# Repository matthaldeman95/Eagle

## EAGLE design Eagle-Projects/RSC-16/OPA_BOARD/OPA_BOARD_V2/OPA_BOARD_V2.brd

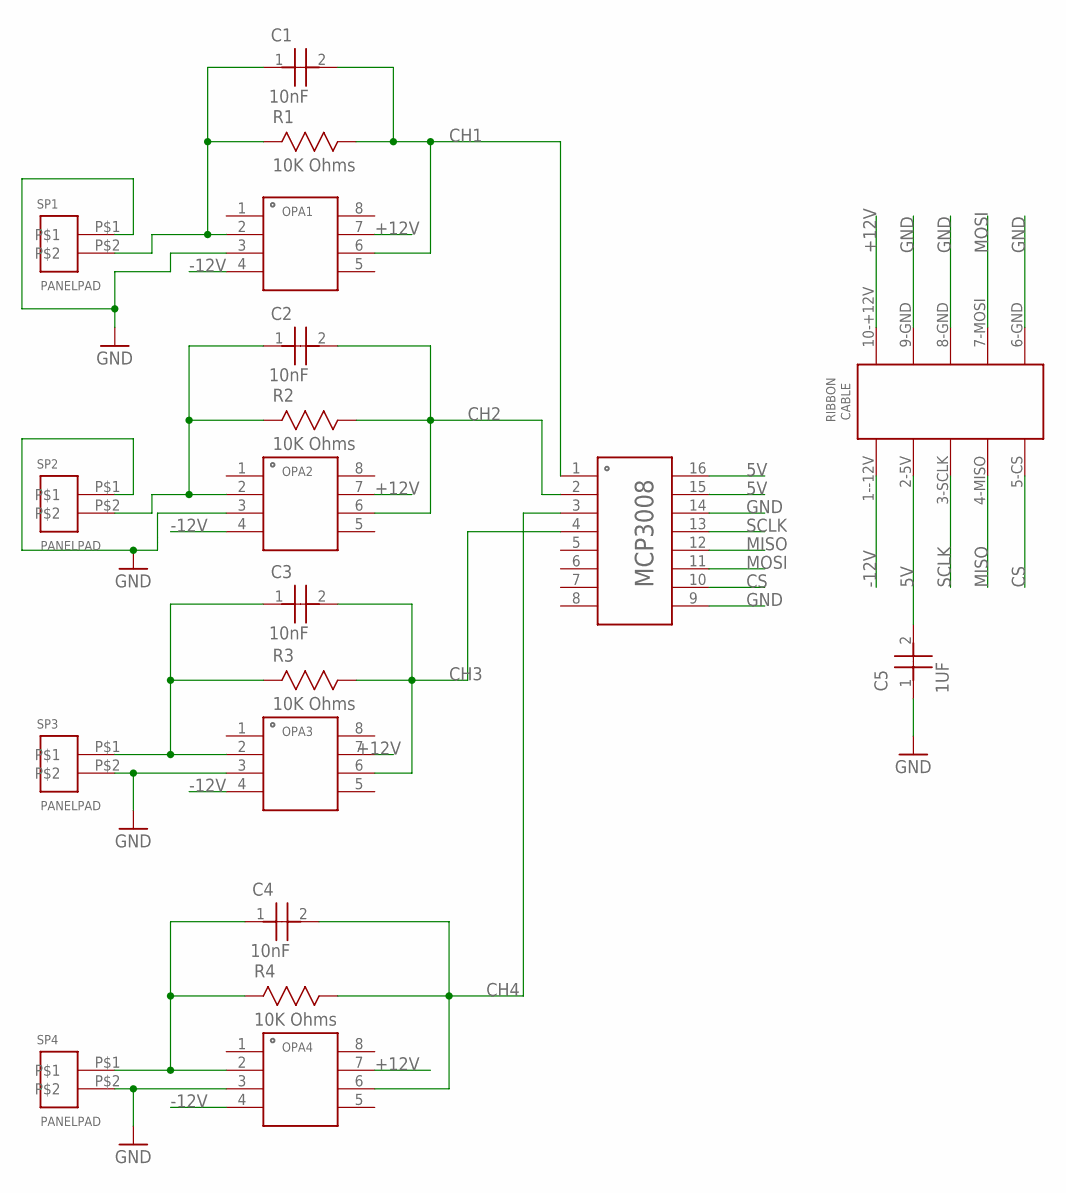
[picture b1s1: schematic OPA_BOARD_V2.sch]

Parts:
ADC: MCP3008-SOIC16; SOIC16N
C1, C2, C3, C4: 10nF; CAP1206
C5: 1UF; CAP1206
OPA1, OPA2, OPA3, OPA4: THS4631-SOIC8; SOIC8
R1, R2, R3, R4: 10K Ohms; RES1206
SP1, SP2, SP3, SP4: PANELPAD; PANELPADS
U$1: 5X2RIBBONCONNECTOR

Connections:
5V: ADC.15 (15-VREF), ADC.16 (16-VDD), C5.2, U$1.2-5V
+12V: OPA1.7 (7-VS+), OPA2.7 (7-VS+), OPA3.7 (7-VS+), OPA4.7 (7-VS+), U$1.10-+12V
-12V: OPA1.4 (4-VS-), OPA2.4 (4-VS-), OPA3.4 (4-VS-), OPA4.4 (4-VS-), U$1.1--12V
CH1: ADC.1 (1-CH0), C1.2, OPA1.6 (6-VOUT), R1.1
CH2: ADC.2 (2-CH1), C2.2, OPA2.6 (6-VOUT), R2.1
CH3: ADC.4 (4-CH3), C3.2, OPA3.6 (6-VOUT), R3.1
CH4: ADC.3 (3-CH2), C4.2, OPA4.6 (6-VOUT), R4.1
CS: ADC.10 (10-CS), U$1.5-CS
GND: ADC.9 (9-DGND), ADC.14 (14-AGND), C5.1, OPA1.3 (3-VIN+), OPA2.3 (3-VIN+), OPA3.3 (3-VIN+), OPA4.3 (3-VIN+), SP1.P$1, SP2.P$1, SP3.P$2, SP4.P$2, U$1.6-GND, U$1.8-GND, U$1.9-GND
MISO: ADC.12 (12-DOUT), U$1.4-MISO
MOSI: ADC.11 (11-DIN), U$1.7-MOSI
unnamed: C3.1, OPA3.2 (2-VIN-), R3.2, SP3.P$1
unnamed: C4.1, OPA4.2 (2-VIN-), R4.2, SP4.P$1
unnamed: C2.1, OPA2.2 (2-VIN-), R2.2, SP2.P$2
unnamed: C1.1, OPA1.2 (2-VIN-), R1.2, SP1.P$2
SCLK: ADC.13 (13-CLK), U$1.3-SCLK

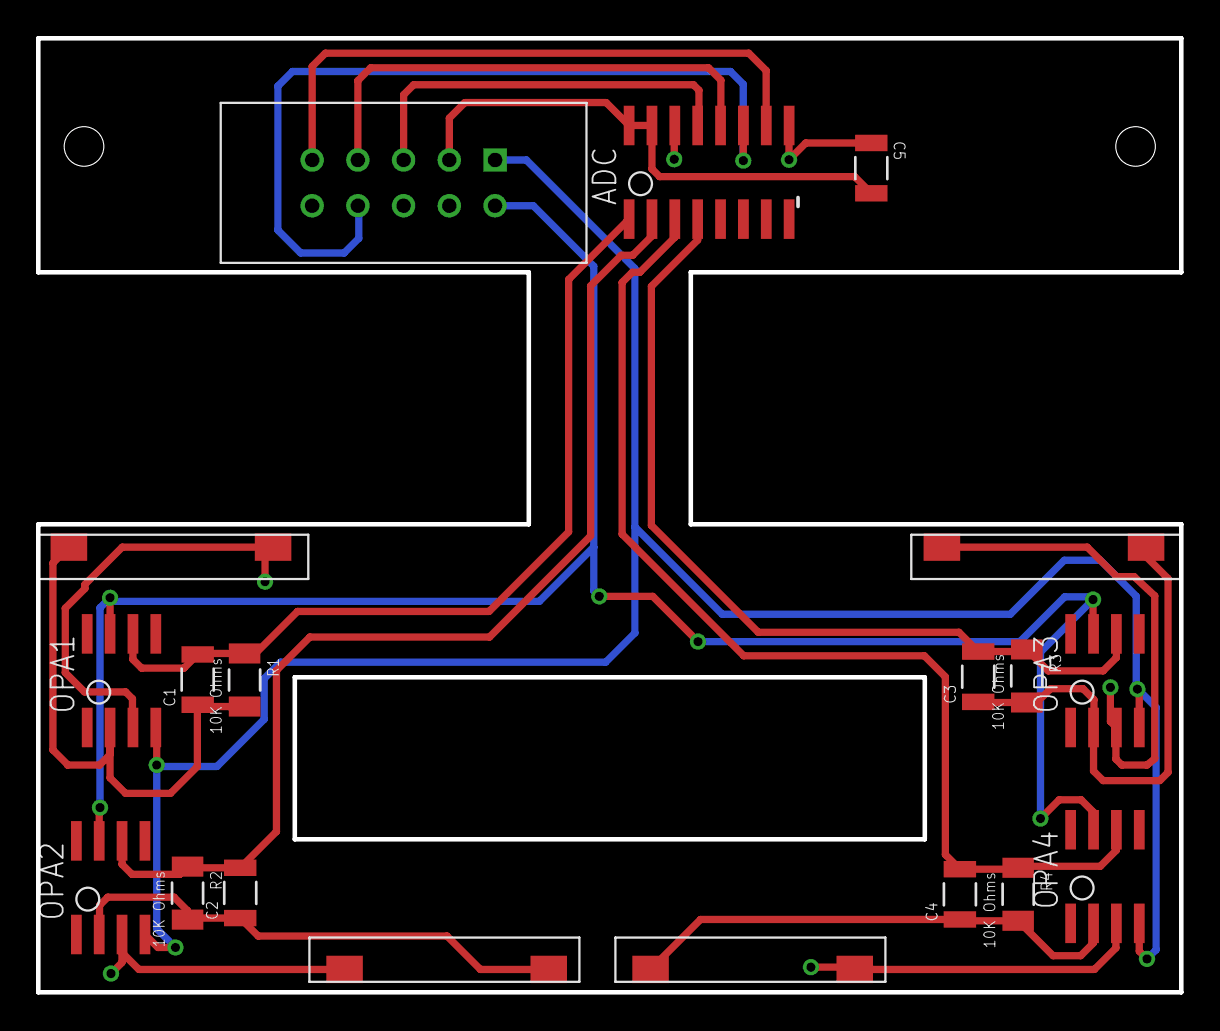
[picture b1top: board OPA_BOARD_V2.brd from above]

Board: 2 copper layers, 63.5 x 53.0 mm, 19 parts (0 on the bottom side), 16 nets.

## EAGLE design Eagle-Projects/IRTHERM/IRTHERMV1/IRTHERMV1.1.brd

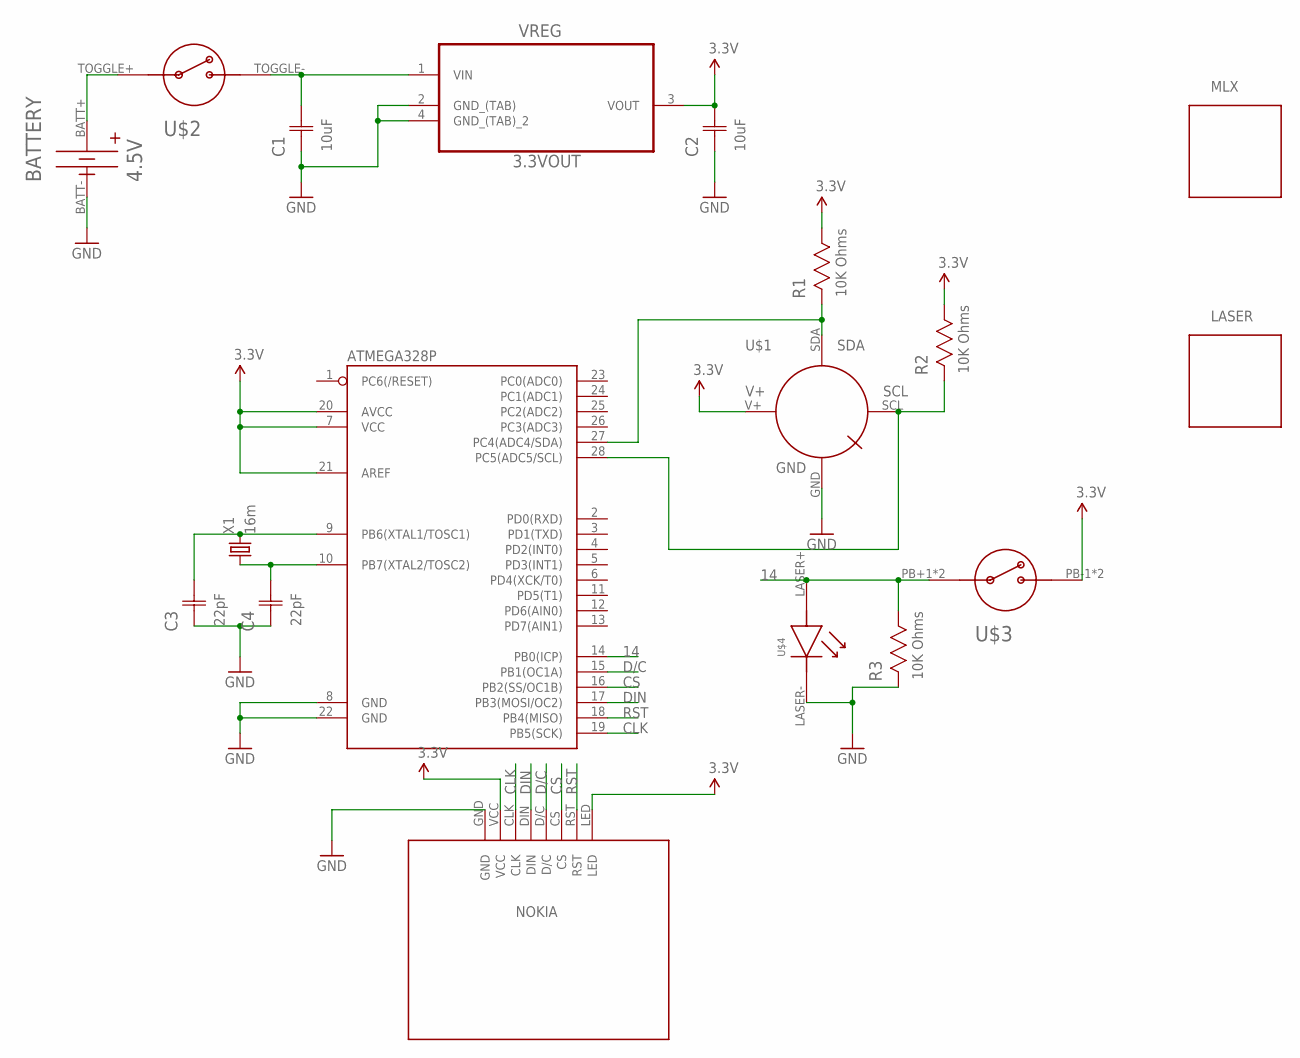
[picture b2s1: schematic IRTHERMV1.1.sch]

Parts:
ATMEGA328P: ATMEGA328P_PDIP; DIL28-3
BATTERY: 4.5V; KEYSTONE2479
C1, C2: 10uF; CAPC3216X180N
C3, C4: 22pF; CAPC3216X88N
LASER: KEYSTONECLIP; KEYSTONE50
MLX: KEYSTONECLIP; KEYSTONE50
R1, R2, R3: 10K Ohms; RESC3216X71N
U$1: MLX90614
U$2: 1683ON-OFFTOGGLE
U$3: 1009PUSHBUTTON
U$4: LASER
U$5: NOKIA
VREG: 3.3VOUT; SOT230P700X180-4N
X1: 16m; HC49US

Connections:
3.3V: ATMEGA328P.7 (VCC), ATMEGA328P.20 (AVCC), ATMEGA328P.21 (AREF), C2.2 (C2), R1.1, R2.1, U$1.V+ (MLXV+), U$3.PB-1 (ONOFF-), U$3.PB-2 (ONOFF-), U$5.LED, U$5.VCC, VREG.3 (VOUT)
14: ATMEGA328P.14 (PB0(ICP)), R3.1, U$3.PB+1 (ONOFF+), U$3.PB+2 (ONOFF+), U$4.LASER+
CLK: ATMEGA328P.19 (PB5(SCK)), U$5.CLK
CS: ATMEGA328P.16 (PB2(SS/OC1B)), U$5.CS
D/C: ATMEGA328P.15 (PB1(OC1A)), U$5.D/C
DIN: ATMEGA328P.17 (PB3(MOSI/OC2)), U$5.DIN
GND: ATMEGA328P.8 (GND), ATMEGA328P.22 (GND), BATTERY.BATT-, C1.1 (C1), C2.1 (C1), C3.1 (C1), C4.1 (C1), R3.2, U$1.GND (MLXGND), U$4.LASER- (LASERGND), U$5.GND, VREG.2 (GND_(TAB)), VREG.4 (GND_(TAB)_2)
unnamed: BATTERY.BATT+, U$2.TOGGLE+ (ONOFF+)
unnamed: C1.2 (C2), U$2.TOGGLE- (ONOFF-), VREG.1 (VIN)
unnamed: ATMEGA328P.27 (PC4(ADC4/SDA)), R1.2, U$1.SDA (MLXSDA)
unnamed: ATMEGA328P.28 (PC5(ADC5/SCL)), R2.2, U$1.SCL (MLXSCL)
unnamed: ATMEGA328P.9 (PB6(XTAL1/TOSC1)), C3.2 (C2), X1.2
unnamed: ATMEGA328P.10 (PB7(XTAL2/TOSC2)), C4.2 (C2), X1.1
RST: ATMEGA328P.18 (PB4(MISO)), U$5.RST

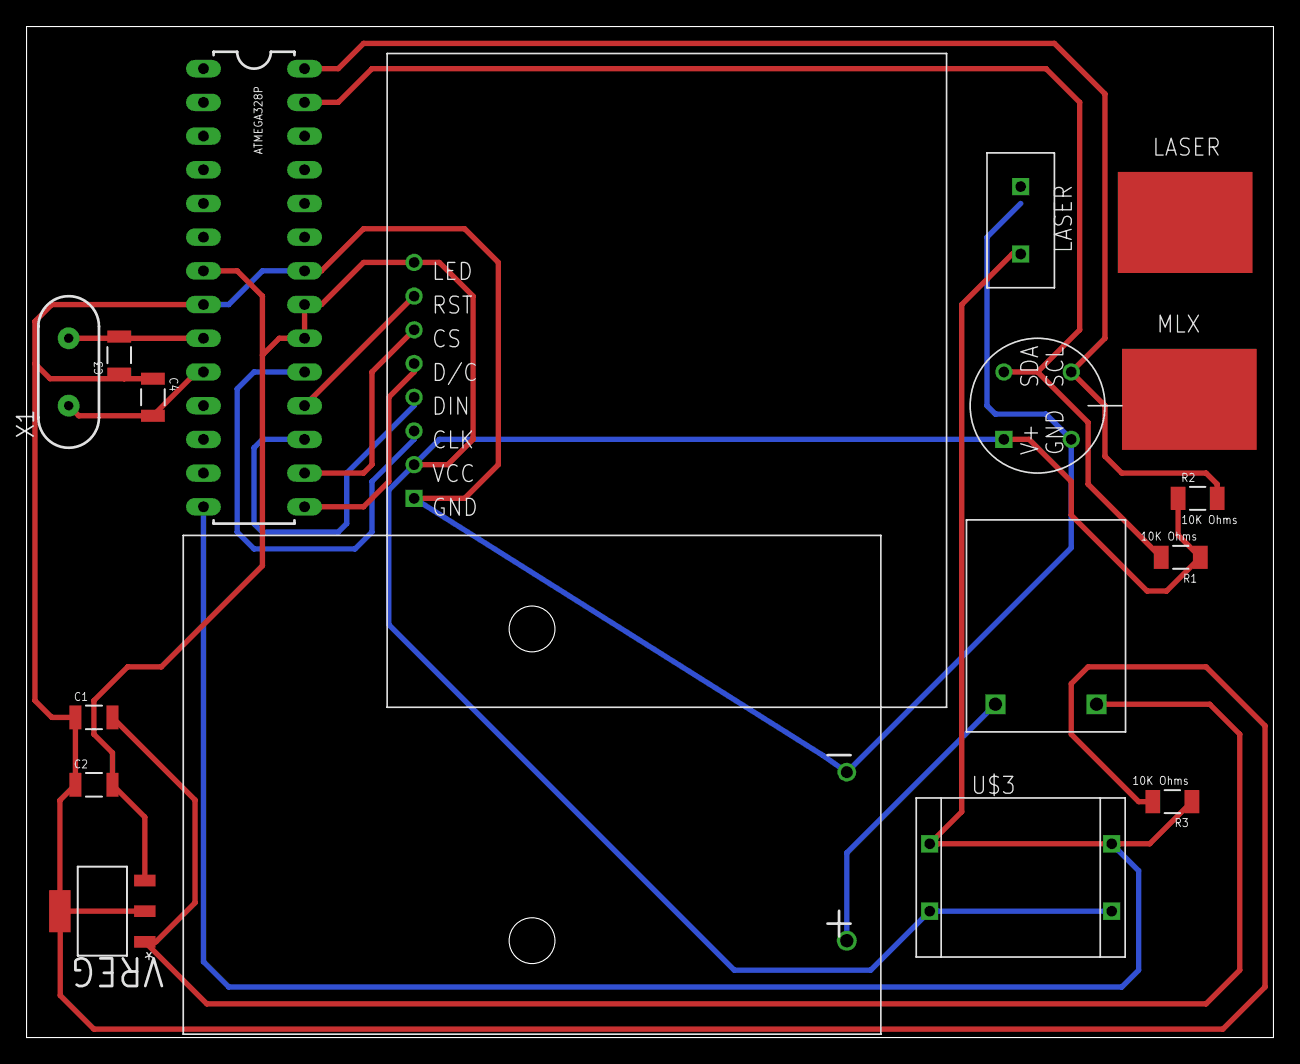
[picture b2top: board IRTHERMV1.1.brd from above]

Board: 2 copper layers, 94.0 x 76.2 mm, 18 parts (0 on the bottom side), 14 nets.

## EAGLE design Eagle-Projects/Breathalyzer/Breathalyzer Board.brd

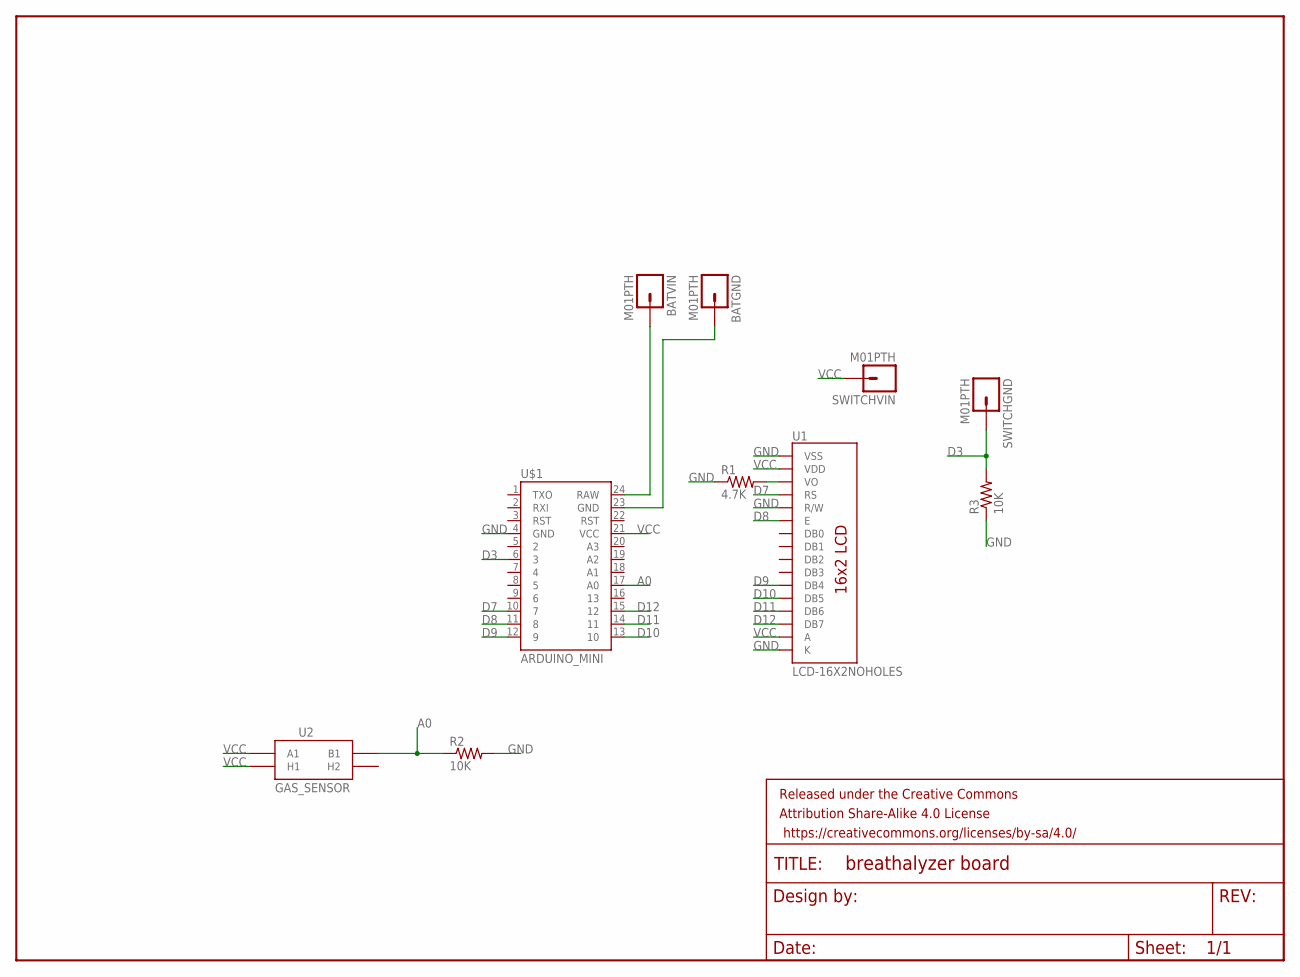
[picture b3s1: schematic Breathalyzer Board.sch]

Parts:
BATGND: M01PTH; 1X01
BATVIN: M01PTH; 1X01
FRAME1: FRAME-LETTER; CREATIVE_COMMONS
R1: 4.7K; AXIAL-0.3
R2, R3: 10K; AXIAL-0.3
SWITCHGND: M01PTH; 1X01
SWITCHVIN: M01PTH; 1X01
U1: LCD-16X2NOHOLES; LCD-16X2_NOHOLES
U2: GAS_SENSOR; MQ-3
U$1: ARDUINO_MINI

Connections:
A0: R2.P$1 (1), U2.B1, U$1.17 (A0)
D3: R3.P$2 (2), SWITCHGND.1, U$1.6 (3)
D7: U1.4 (RS), U$1.10 (7)
D8: U1.6 (E), U$1.11 (8)
D9: U1.11 (DB4), U$1.12 (9)
D10: U1.12 (DB5), U$1.13 (10)
D11: U1.13 (DB6), U$1.14 (11)
D12: U1.14 (DB7), U$1.15 (12)
GND: R1.P$1 (1), R2.P$2 (2), R3.P$1 (1), U1.1 (VSS), U1.5 (R/W), U1.16 (K), U$1.4 (GND)
unnamed: BATVIN.1, U$1.24 (RAW)
unnamed: BATGND.1, U$1.23 (GND)
unnamed: R1.P$2 (2), U1.3 (VO)
VCC: SWITCHVIN.1, U1.2 (VDD), U1.15 (A), U2.A1, U2.HA (H1), U$1.21 (VCC)

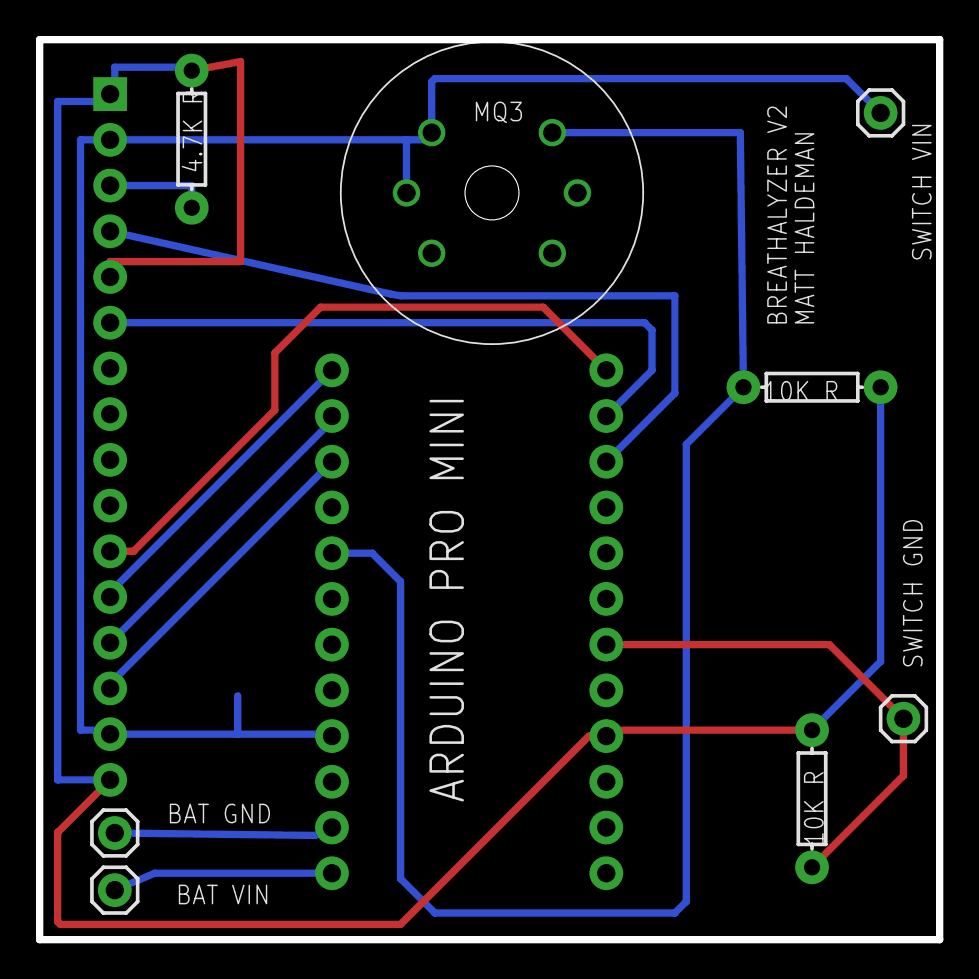
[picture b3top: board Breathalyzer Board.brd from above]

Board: 2 copper layers, 50.0 x 50.0 mm, 11 parts (1 on the bottom side), 13 nets.

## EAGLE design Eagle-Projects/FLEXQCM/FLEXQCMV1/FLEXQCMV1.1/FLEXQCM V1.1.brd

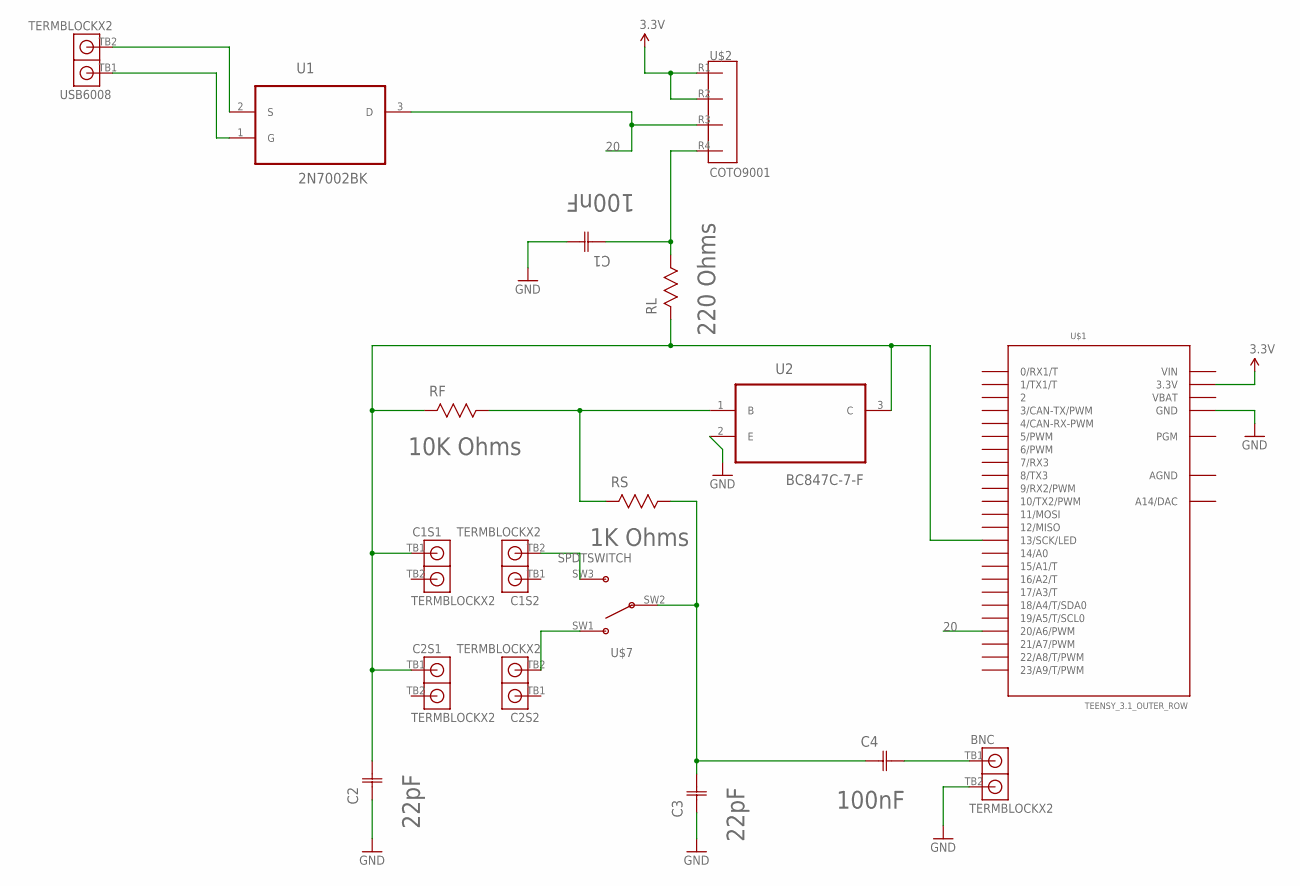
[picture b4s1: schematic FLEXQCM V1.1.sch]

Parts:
BNC: TERMBLOCKX2
C1, C4: 100nF; CAPC3216X88N
C1S1, C1S2, C2S1, C2S2: TERMBLOCKX2
C2, C3: 22pF; CAPC3216X88N
RF: 10K Ohms; RESC3216X71N
RL: 220 Ohms; RESC3216X71N
RS: 1K Ohms; RESC3216X71N
U1: 2N7002BK; SOT95P230X110-3N
U2: BC847C-7-F; SOT103P240X110-3N
U$1: TEENSY_3.1_OUTER_ROW; TEENSY3-OUTER_ROW
U$2: COTO9001
U$7: SPDTSWITCH
USB6008: TERMBLOCKX2

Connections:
3V3: U$1.3.3V, U$1.3.3V1 (3.3V), U$2.R1, U$2.R2
13: C1S1.TB1, C2.2 (C2), C2S1.TB1, RF.2, RL.2, U2.3 (C), U$1.13 (13/SCK/LED)
20: U1.3 (D), U$1.20/A6 (20/A6/PWM), U$2.R3
AGND: U$1.AGND
GND: BNC.TB2, C1.2 (C2), C2.1 (C1), C3.1 (C1), U2.2 (E), U$1.GND, U$1.GND1 (GND)
unnamed: U1.2 (S), USB6008.TB2
unnamed: U1.1 (G), USB6008.TB1
unnamed: C1.1 (C1), RL.1, U$2.R4
unnamed: C1S2.TB2, U$7.SW3
unnamed: RF.1, RS.2, U2.1 (B)
unnamed: C2S2.TB2, U$7.SW1
unnamed: C3.2 (C2), C4.1 (C1), RS.1, U$7.SW2
unnamed: BNC.TB1, C4.2 (C2)
VBAT: U$1.VBAT
VIN: U$1.VIN

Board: 2 copper layers, 18 parts (0 on the bottom side), 12 nets, no tracks yet.

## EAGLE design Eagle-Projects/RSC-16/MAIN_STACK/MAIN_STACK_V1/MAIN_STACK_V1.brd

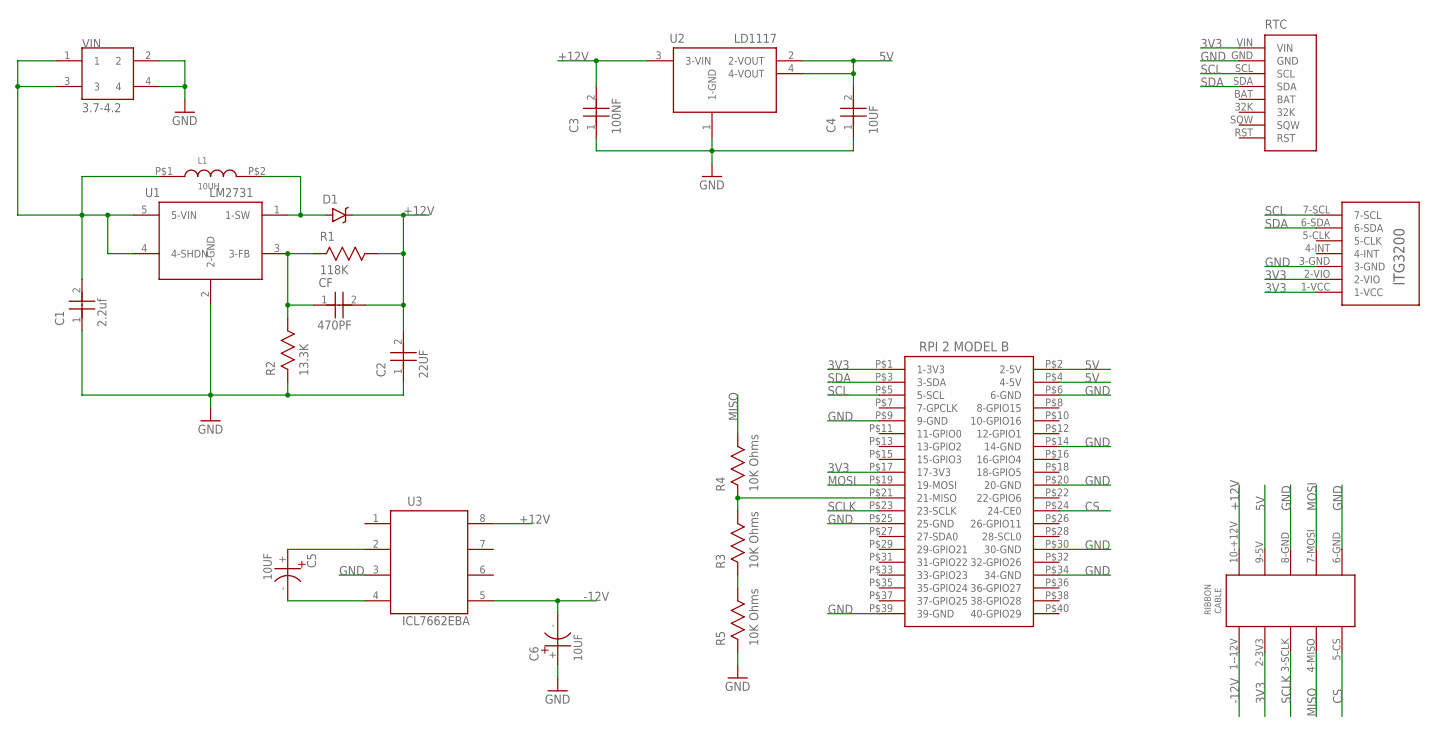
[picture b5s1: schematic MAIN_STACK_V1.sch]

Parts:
C1: 2.2uf; CAP1206
C2: 22UF; CAP1206
C3: 100NF; CAP1206
C4: 10UF; CAP1206
C5, C6: 10UF; KEMET9BPOLCAP
CF: 470PF; CAP1206
D1: DIODE-SCHOTTKY; SOD-123
L1: 10UH; CDRH125NP
R1: 118K; RES1206
R2: 13.3K; RES1206
R3, R4, R5: 10K Ohms; RES1206
RTC: DS3231BREAKOUT
U1: LM2731; SOT95
U2: LD1117; SOT223
U3: ICL7662EBA; SOIC8
U$1: RPI2
U$2: ITG3200
U$3: 5X2RIBBONCONNECTOR
VIN: 3.7-4.2; HIROSEPOWERCONNECTOR

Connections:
3V3: RTC.VIN, U$1.P$1 (1-3V3), U$1.P$17 (17-3V3), U$2.1-VCC, U$2.2-VIO, U$3.2-3V3
5V: C4.2, U2.2 (2-VOUT), U2.4 (4-VOUT), U$1.P$2 (2-5V), U$1.P$4 (4-5V), U$3.9-5V
+12V: C2.2, C3.2, CF.2, D1.C, R1.1, U2.3 (3-VIN), U3.8 (8-V+), U$3.10-+12V
-12V: C6.-, U3.5 (5-VOUT), U$3.1--12V
CS: U$1.P$24 (24-CE0), U$3.5-CS
GND: C1.1, C2.1, C3.1, C4.1, C6.+, R2.2, R5.2, RTC.GND, U1.2 (2-GND), U2.1 (1-GND), U3.3 (3-GND), U$1.P$6 (6-GND), U$1.P$9 (9-GND), U$1.P$14 (14-GND), U$1.P$20 (20-GND), U$1.P$25 (25-GND), U$1.P$30 (30-GND), U$1.P$34 (34-GND), U$1.P$39 (39-GND), U$2.3-GND, U$3.6-GND, U$3.8-GND, VIN.2, VIN.4
MISO: R4.1, U$3.4-MISO
MOSI: U$1.P$19 (19-MOSI), U$3.7-MOSI
unnamed: C5.+, U3.2 (2-CAP+)
unnamed: D1.A, L1.P$2 (2), U1.1 (1-SW)
unnamed: C5.-, U3.4 (4-CAP-)
unnamed: CF.1, R1.2, R2.1, U1.3 (3-FB)
unnamed: R3.1, R4.2, U$1.P$21 (21-MISO)
unnamed: R3.2, R5.1
SCL: RTC.SCL, U$1.P$5 (5-SCL), U$2.7-SCL
SCLK: U$1.P$23 (23-SCLK), U$3.3-SCLK
SDA: RTC.SDA, U$1.P$3 (3-SDA), U$2.6-SDA
VIN: C1.2, L1.P$1 (1), U1.4 (4-SHDN), U1.5 (5-VIN), VIN.1, VIN.3

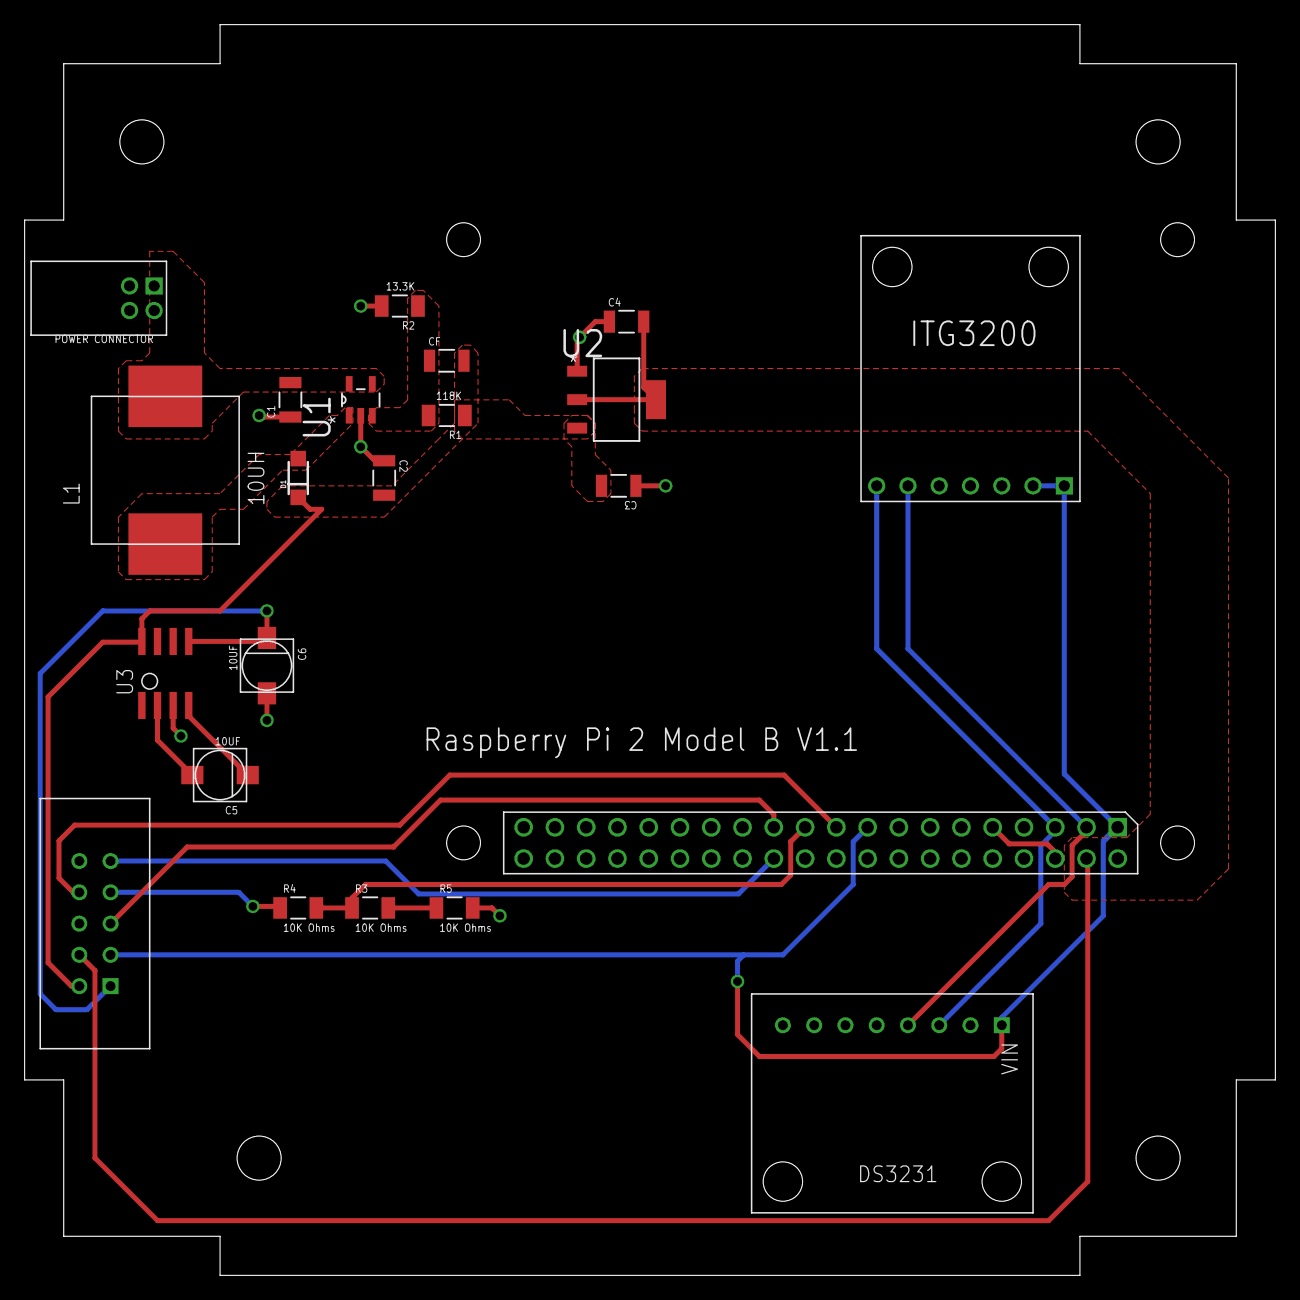
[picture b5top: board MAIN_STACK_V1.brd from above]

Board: 2 copper layers, 101.6 x 101.6 mm, 22 parts (0 on the bottom side), 18 nets.

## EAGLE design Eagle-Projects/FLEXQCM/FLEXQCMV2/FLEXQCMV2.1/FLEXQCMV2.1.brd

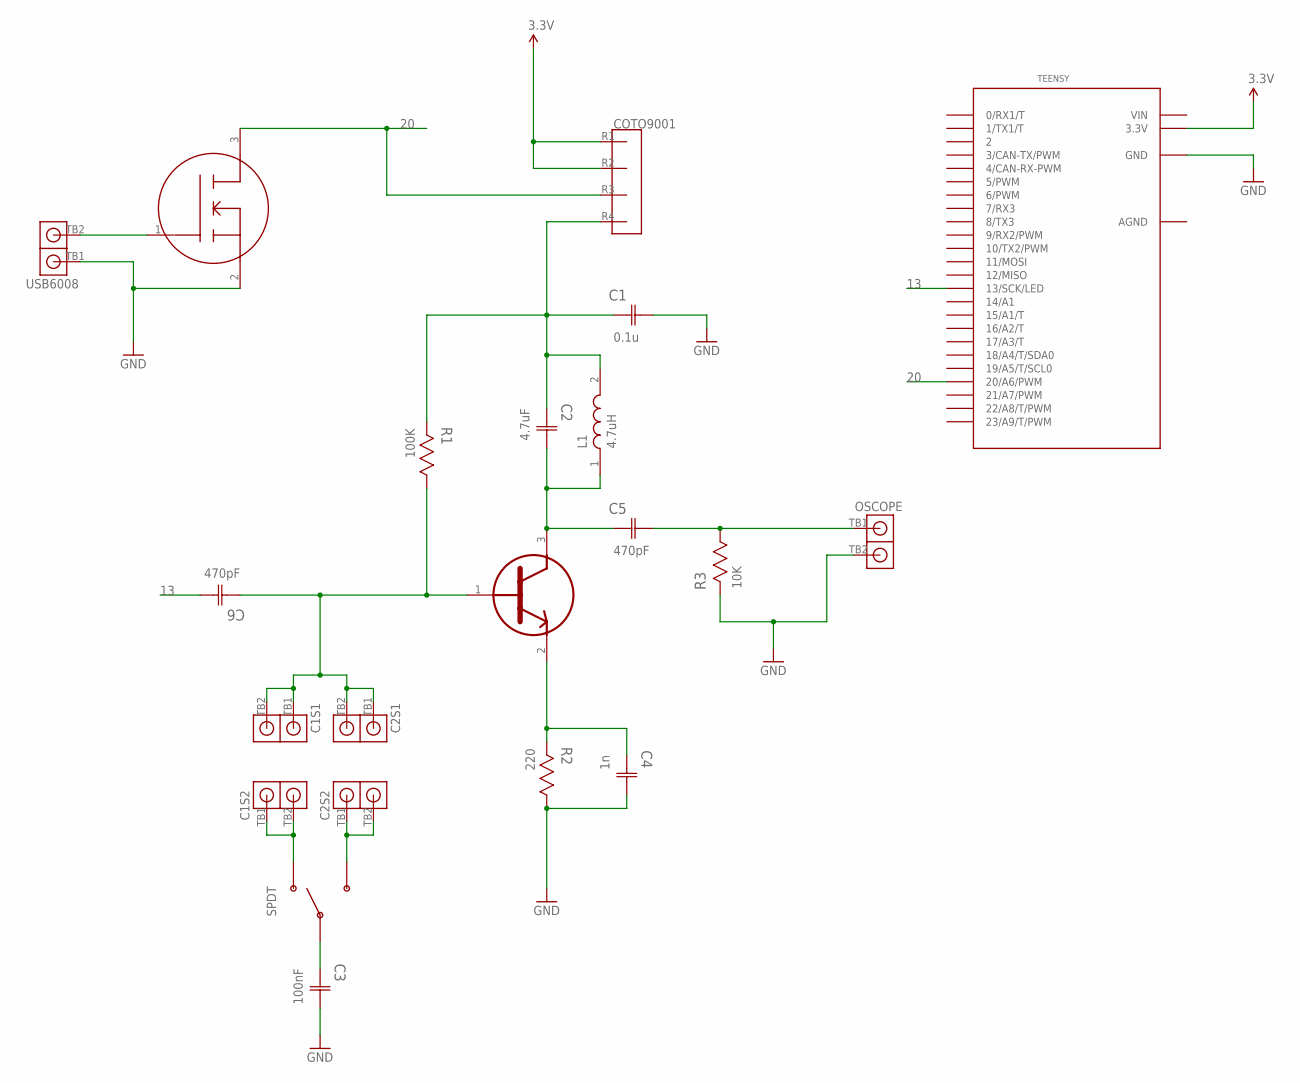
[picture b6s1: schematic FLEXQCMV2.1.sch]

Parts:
C1: 0.1u; CAPC3216X88N
C1S1, C1S2, C2S1, C2S2: TERMBLOCKX2
C2: 4.7uF; CAPC3216X180N
C3: 100nF; CAPC3216X88N
C4: 1n; CAPC3216X88N
C5, C6: 470pF; CAPC3216X100N
COTO9001: COTO9001
L1: 4.7uH; INDC3225X210N
OSCOPE: TERMBLOCKX2
R1: 100K; RESC3216X71N
R2: 220; RESC3216X71N
R3: 10K; RESC3216X71N
SPDT: SPDTSWITCH
TEENSY: TEENSY_3.1_DIL; TEENSY3-DIL
U1: FET; SOT95P230X110-3N
U2: BJT; SOT95P230X110-3N
USB6008: TERMBLOCKX2

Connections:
3.3V: COTO9001.R1, COTO9001.R2, TEENSY.3.3V
13: C6.2 (C2), TEENSY.13 (13/SCK/LED)
20: COTO9001.R3, TEENSY.20/A6 (20/A6/PWM), U1.3 (D)
AGND: TEENSY.AGND
GND: C1.2 (C2), C3.2 (C2), C4.2 (C2), OSCOPE.TB2, R2.1, R3.2, TEENSY.GND, U1.2 (S), USB6008.TB1
unnamed: U1.1 (G), USB6008.TB2
unnamed: C4.1 (C1), R2.2, U2.2 (E)
unnamed: C1S2.TB1, C1S2.TB2, SPDT.SW1
unnamed: C1.1 (C1), C2.1 (C1), COTO9001.R4, L1.2, R1.2
unnamed: C1S1.TB1, C1S1.TB2, C2S1.TB1, C2S1.TB2, C6.1 (C1), R1.1, U2.1 (B)
unnamed: C2S2.TB1, C2S2.TB2, SPDT.SW3
unnamed: C3.1 (C1), SPDT.SW2
unnamed: C2.2 (C2), C5.1 (C1), L1.1, U2.3 (C)
unnamed: C5.2 (C2), OSCOPE.TB1, R3.1
VIN: TEENSY.VIN

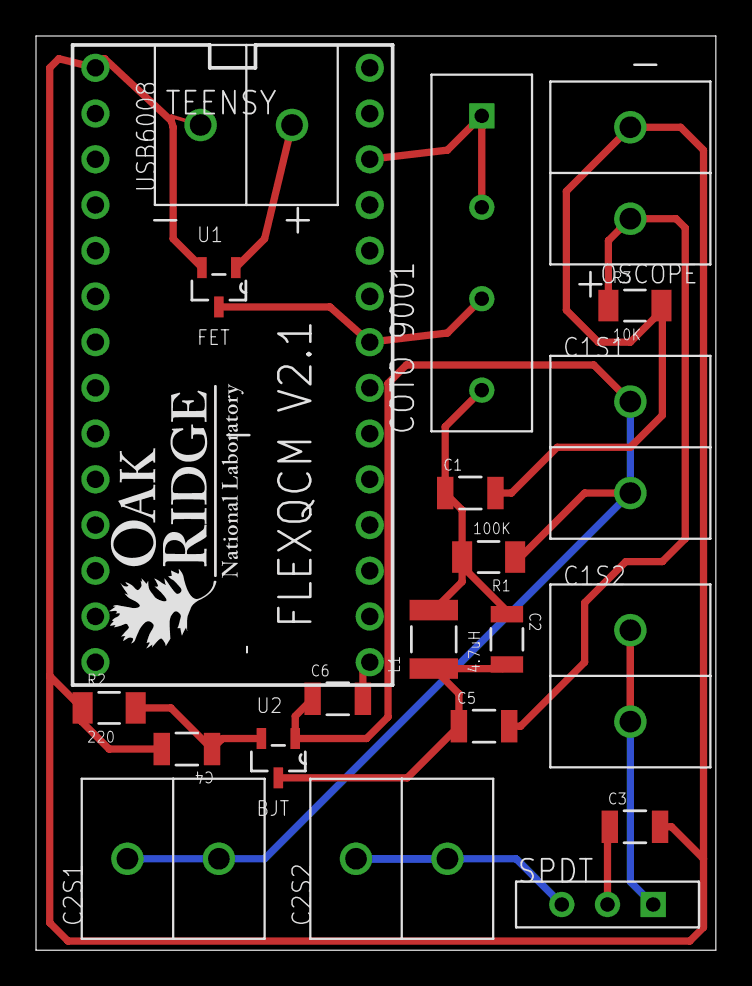
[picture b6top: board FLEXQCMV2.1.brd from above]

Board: 2 copper layers, 37.8 x 50.8 mm, 22 parts (0 on the bottom side), 13 nets.

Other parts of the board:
U$1: ORNLLOGOV9

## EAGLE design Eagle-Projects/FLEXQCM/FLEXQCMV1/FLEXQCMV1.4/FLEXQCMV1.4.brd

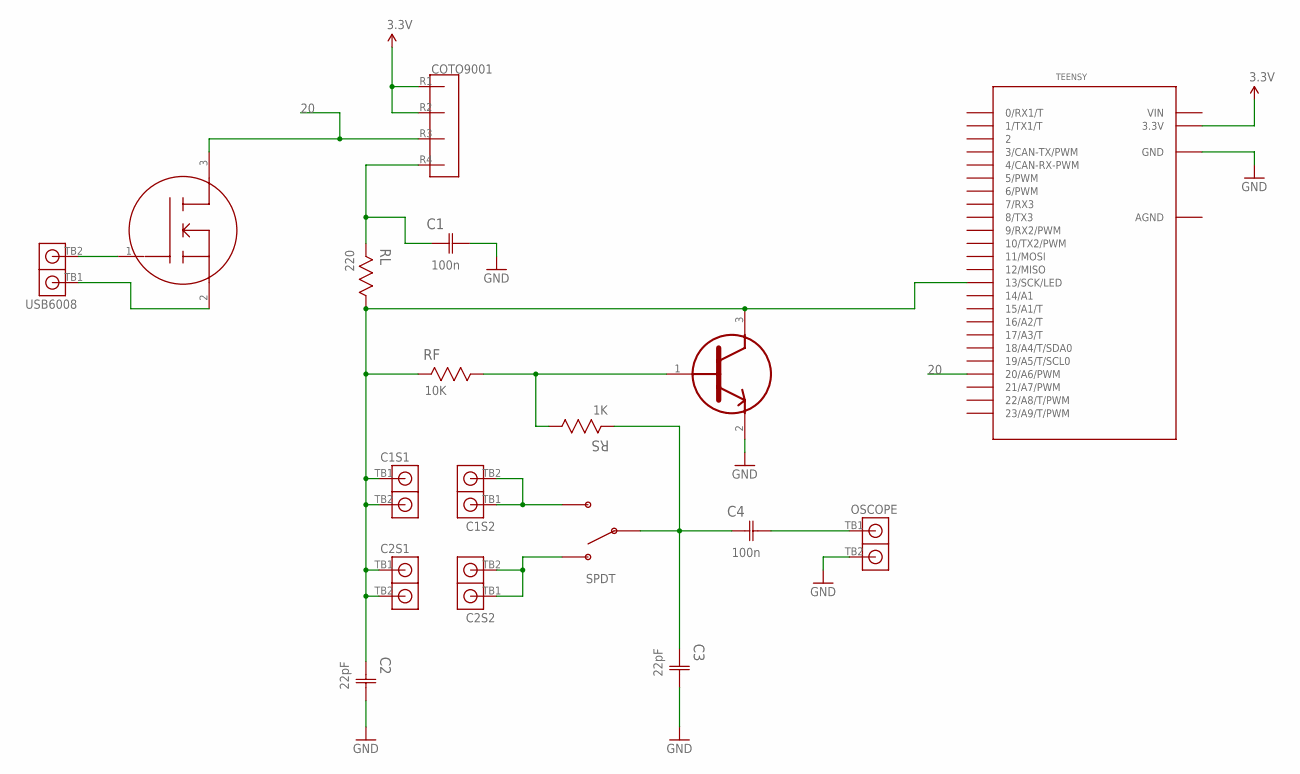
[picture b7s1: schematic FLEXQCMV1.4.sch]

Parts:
C1, C4: 100n; CAPC3216X88N
C1S1, C1S2, C2S1, C2S2: TERMBLOCKX2
C2, C3: 22pF; CAPC3216X88N
COTO9001: COTO9001
OSCOPE: TERMBLOCKX2
RF: 10K; RESC3216X71N
RL: 220; RESC3216X71N
RS: 1K; RESC3216X71N
SPDT: SPDTSWITCH
TEENSY: TEENSY_3.1_DIL; TEENSY3-DIL
U1: FET; SOT95P230X110-3N
U2: BJT; SOT95P230X110-3N
USB6008: TERMBLOCKX2

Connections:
3.3V: COTO9001.R1, COTO9001.R2, TEENSY.3.3V
20: COTO9001.R3, TEENSY.20/A6 (20/A6/PWM), U1.3 (D)
AGND: TEENSY.AGND
GND: C1.2 (C2), C2.2 (C2), C3.2 (C2), OSCOPE.TB2, TEENSY.GND, U2.2 (E)
unnamed: U1.1 (G), USB6008.TB2
unnamed: U1.2 (S), USB6008.TB1
unnamed: C1.1 (C1), COTO9001.R4, RL.2
unnamed: C1S2.TB1, C1S2.TB2, SPDT.SW3
unnamed: RF.1, RS.1, U2.1 (B)
unnamed: C2S2.TB1, C2S2.TB2, SPDT.SW1
unnamed: C1S1.TB1, C1S1.TB2, C2.1 (C1), C2S1.TB1, C2S1.TB2, RF.2, RL.1, TEENSY.13 (13/SCK/LED), U2.3 (C)
unnamed: C4.2 (C2), OSCOPE.TB1
unnamed: C3.1 (C1), C4.1 (C1), RS.2, SPDT.SW2
VIN: TEENSY.VIN

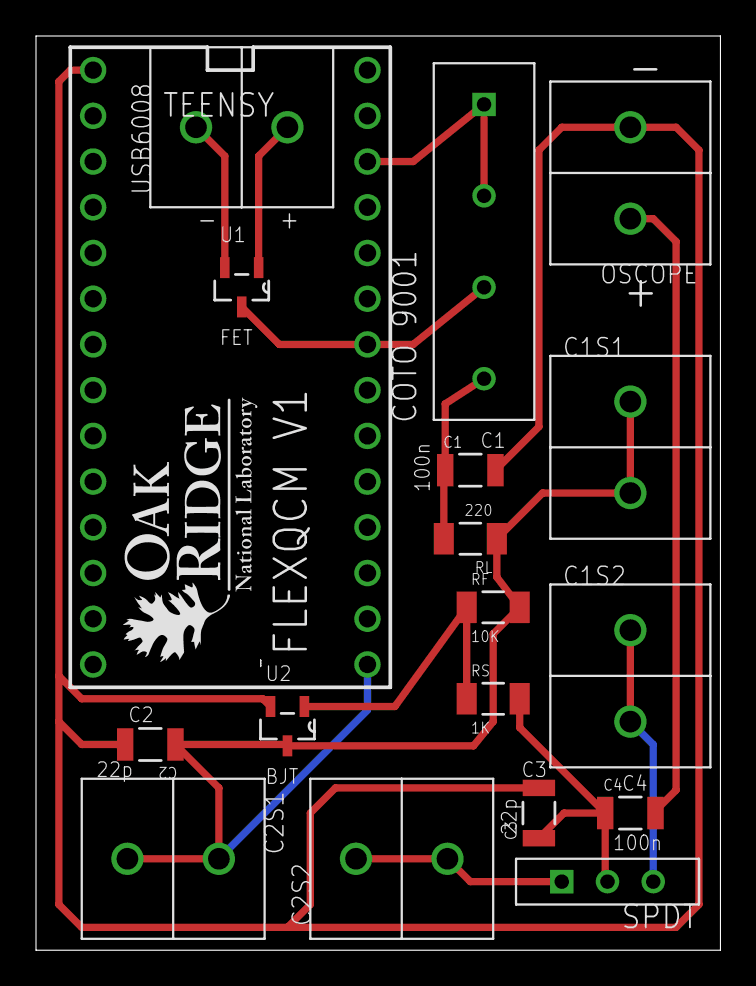
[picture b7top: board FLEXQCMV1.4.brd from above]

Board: 2 copper layers, 38.0 x 50.8 mm, 19 parts (0 on the bottom side), 12 nets.

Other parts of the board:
U$1: ORNLLOGOV9

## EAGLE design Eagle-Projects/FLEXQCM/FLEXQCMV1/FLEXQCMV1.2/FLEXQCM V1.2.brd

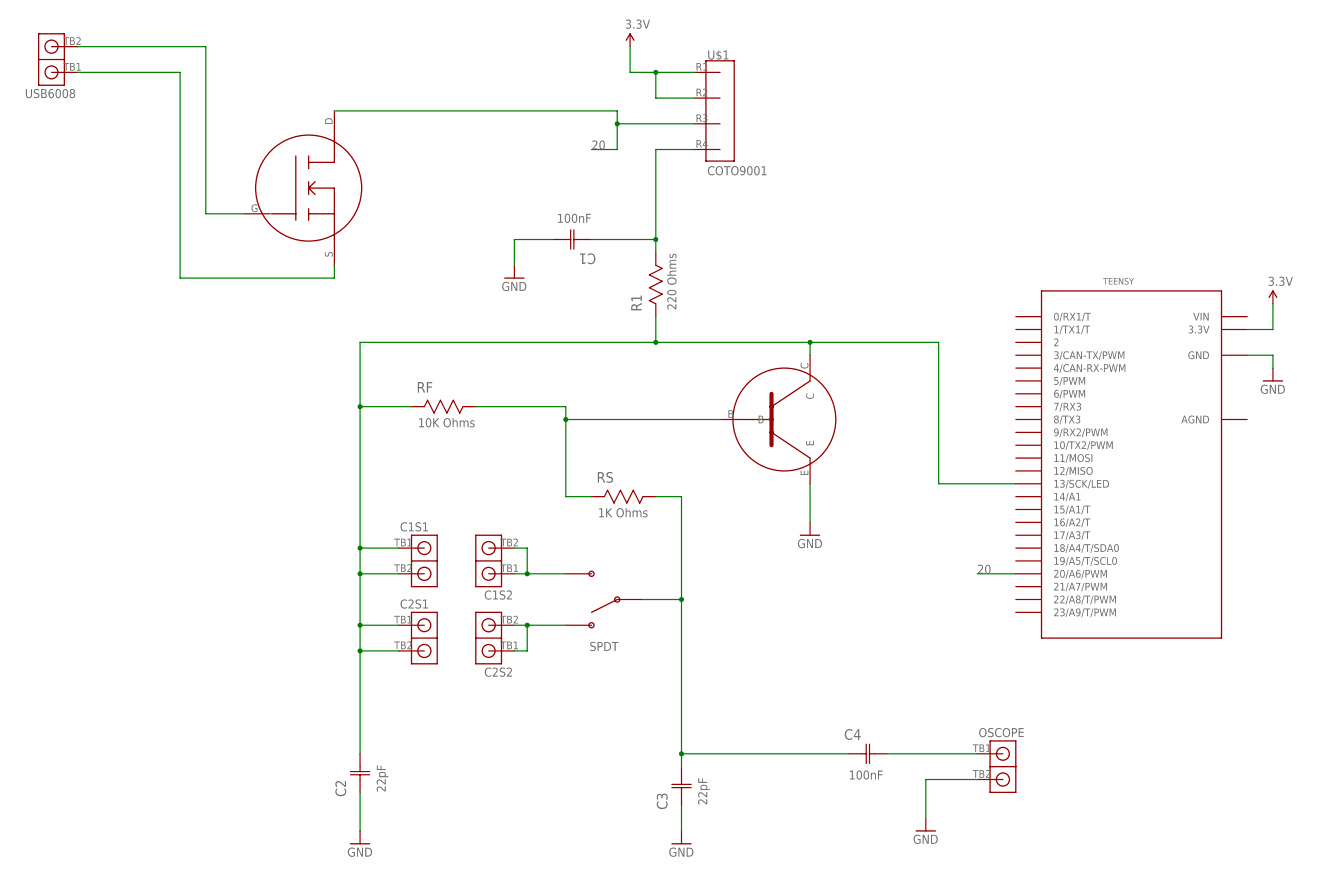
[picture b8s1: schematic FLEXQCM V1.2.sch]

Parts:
C1, C4: 100nF; CAPC3216X88N
C1S1, C1S2, C2S1, C2S2: TERMBLOCKX2
C2, C3: 22pF; CAPC3216X88N
OSCOPE: TERMBLOCKX2
R1: 220 Ohms; RESC3216X71N
RF: 10K Ohms; RESC3216X71N
RS: 1K Ohms; RESC3216X71N
SPDT: SPDTSWITCH
TEENSY: TEENSY_3.1_DIL; TEENSY3-DIL
U1: 2N7002BK; SOT95P230X110-3N
U2: BC847C-7-F; SOT103P240X110-3N
U$1: COTO9001
USB6008: TERMBLOCKX2

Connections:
3V3: TEENSY.3.3V, U$1.R1, U$1.R2
13: C1S1.TB1, C1S1.TB2, C2.2 (C2), C2S1.TB1, C2S1.TB2, R1.2, RF.2, TEENSY.13 (13/SCK/LED), U2.C
20: TEENSY.20/A6 (20/A6/PWM), U1.D, U$1.R3
AGND: TEENSY.AGND
GND: C1.2 (C2), C2.1 (C1), C3.1 (C1), OSCOPE.TB2, TEENSY.GND, U2.E
unnamed: U1.G, USB6008.TB2
unnamed: U1.S, USB6008.TB1
unnamed: C1S2.TB1, C1S2.TB2, SPDT.SW3
unnamed: C1.1 (C1), R1.1, U$1.R4
unnamed: C2S2.TB1, C2S2.TB2, SPDT.SW1
unnamed: RF.1, RS.2, U2.B
unnamed: C4.2 (C2), OSCOPE.TB1
unnamed: C3.2 (C2), C4.1 (C1), RS.1, SPDT.SW2
VIN: TEENSY.VIN

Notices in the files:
parts and their libraries:
SparkFun-Connectors: Licensing: Creative Commons ShareAlike 4.0 International - https://creativecommons.org/licenses/by-sa/4.0
SparkFun-Aesthetics: Released under the Creative Commons Attribution Share-Alike 4.0 License
SparkFun-Aesthetics: https://creativecommons.org/licenses/by-sa/4.0
